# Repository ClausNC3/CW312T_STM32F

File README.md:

# CW312T-STM32F

This board supports the STMicroelectronics STM32F microcontroller. The default build
has the STMicroelectronics STM32F405VGT6, which has 1MB flash and 192kB SRAM.

---

## Specifications

|Feature|Notes/Range|
|-|-|
|Target Device|STM32F405VGT6|
|Target Architecture|Arm Cortex-M4|
|Vcc|3.3V|
|Programming|STM32F Serial Bootloader, JTAG or SWD|
|Hardware Crypto|No|
|Availability|Standalone|
|Status|Released|
|Shunt|10Ω|

---

## Power Supply

---

## Programming

### **ChipWhisperer Programmer via Bootloader**

See further down this page for details.

### **JTAG Programmer**

The 20-pin JTAG port (HDR6 on CW313 Board) can be used with the
[ST-LINK/V2](https://www.digikey.com/product-detail/en/stmicroelectronics/ST-LINK-V2/497-10484-ND/2214535)
which is a low-cost JTAG programmer.

It is also possible to use other JTAG programmers such as OpenOCD. The
following command worked with an Olimex OpenOCD programmer and their
[OpenOCD for
Windows](https://www.olimex.com/Products/ARM/JTAG/ARM-USB-OCD-H/)
software:

    openocd
      -f path/to/board/files/cw313.cfg
      -c init
      -c targets
      -c "halt"
      -c "flash write_image erase path/to/firmware.hex"
      -c "verify_image path/to/firmware.hex"
      -c "reset run"
      -c shutdown

where the contents of `cw313.cfg` are

    source [find interface/olimex-arm-usb-ocd-h.cfg]
    source [find target/stm32f4x.cfg]
    reset_config srst_only

### **Programming via ChipWhisperer Bootloader**

The STM32F devices have a built-in bootloader, and the ChipWhisperer
software as of 3.5.2 includes support for this bootloader.

Important notes before we begin:

  - You MUST setup a clock and the serial lines for the chip. This is
    easily done by connecting to the scope and target, then running
    `default_setup()`:

<!-- end list -->

``` python
import chipwhisperer as cw
scope = cw.scope
target = cw.target(scope)
scope.default_setup()
```

Run the following python code once you have the scope and target set up:

``` python
prog = cw.programmers.STM32FProgrammer
cw.program_target(scope, prog, "<path to fw hex file>")
```

---

## Schematic

The schematic is available as a [PDF](CW312T-STM32F.pdf) or below as an image:

---

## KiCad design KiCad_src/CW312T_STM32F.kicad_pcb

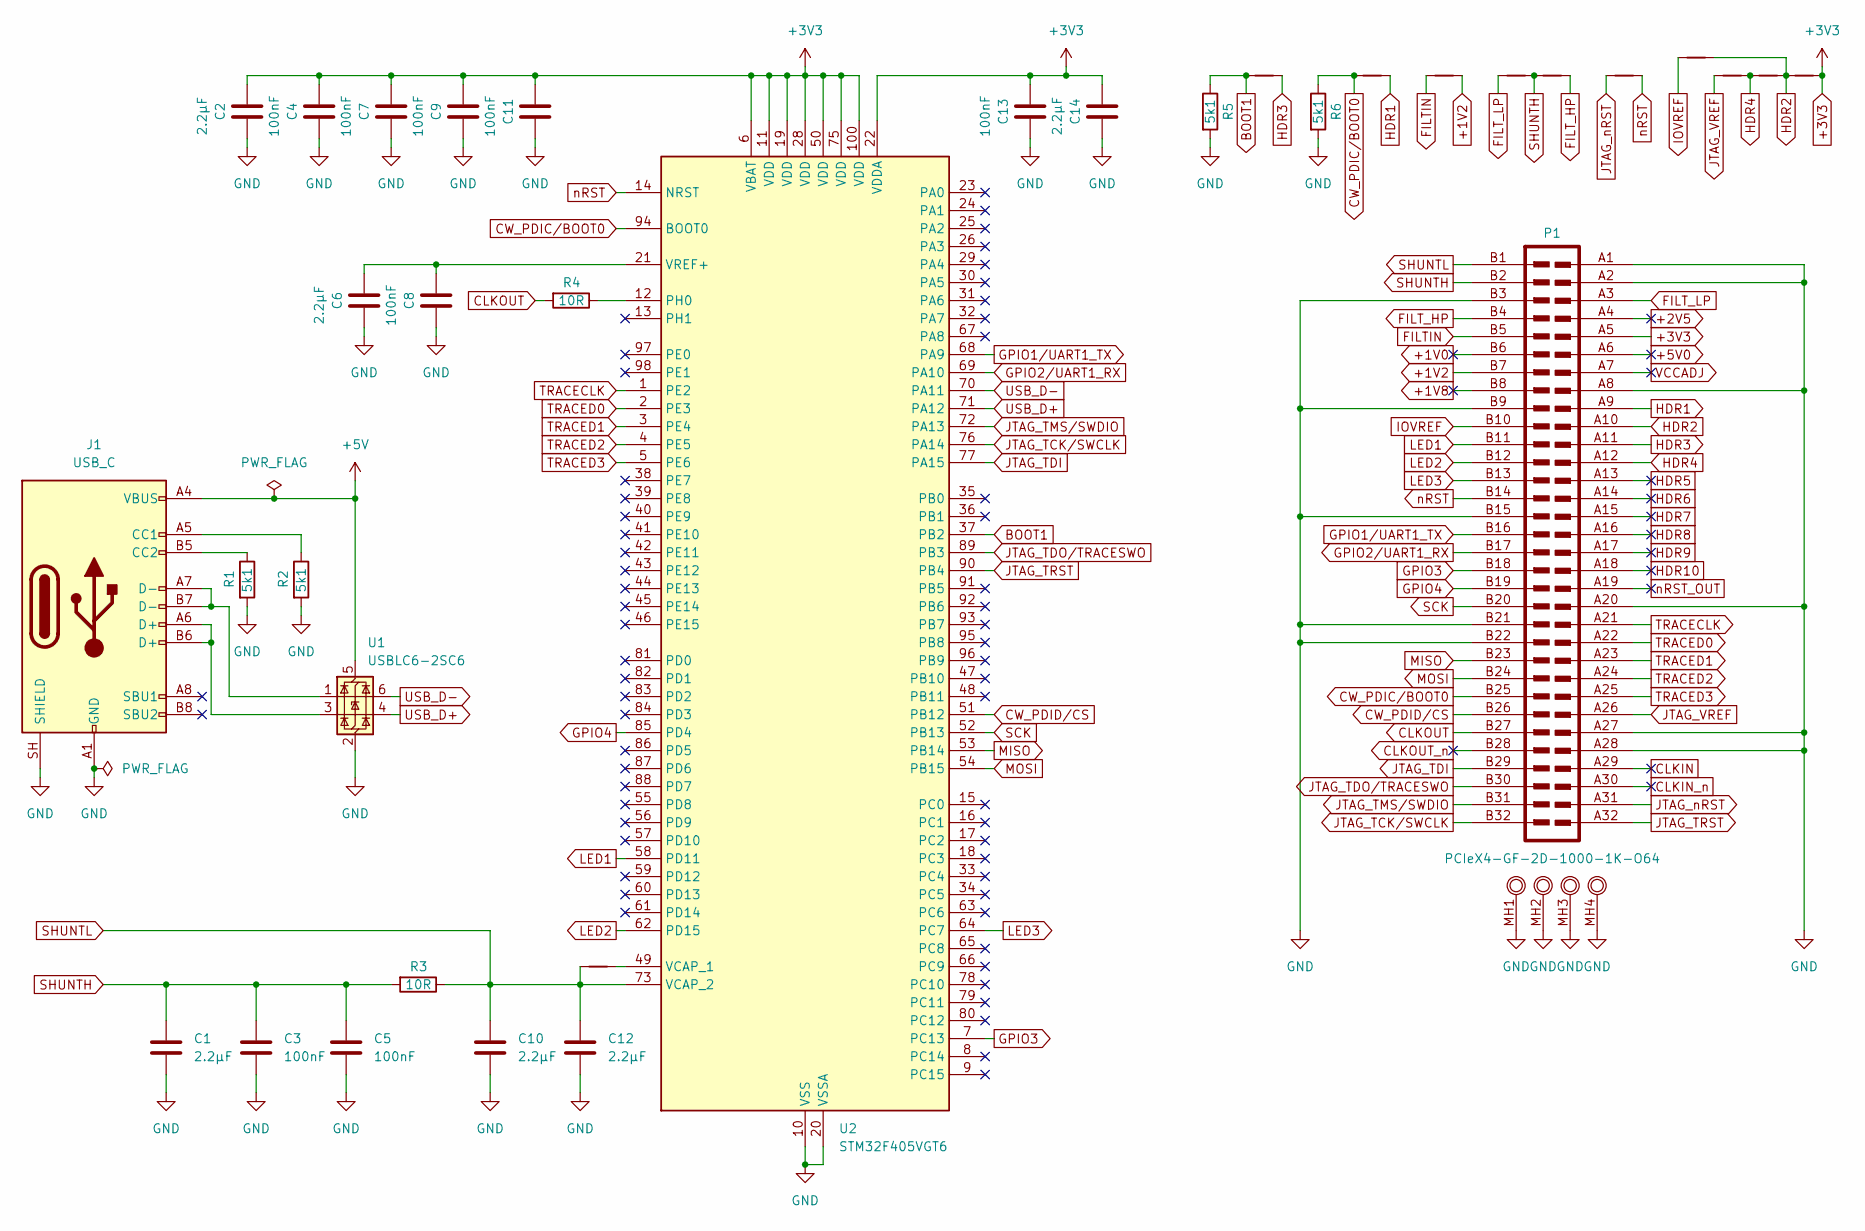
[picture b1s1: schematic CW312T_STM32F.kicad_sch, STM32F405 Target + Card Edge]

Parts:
C1, C2, C6, C10, C12, C14: 2.2μF; C_0603_1608Metric
C3, C4, C5, C7, C8, C9, C11, C13: 100nF; C_0603_1608Metric
J1: USB_C; USB_C_Receptacle_GCT_USB4105-xx-A_16P_TopMnt_Horizontal
NT1, NT2, NT3, NT4, NT5, NT6, NT7, NT8, NT9, NT10, NT11: NetTie_2; NetTie-2_SMD_Pad0.5mm
P1: PCIeX4-GF-2D-1000-1K-O64; CW312_CardEdge
R1, R2, R5, R6: 5k1; R_0603_1608Metric
R3, R4: 10R; R_0603_1608Metric
U1: USBLC6-2SC6; SOT-23-6
U2: STM32F405VGT6; LQFP-100_14x14mm_P0.5mm

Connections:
+1V0: P1.B6
+1V2: NT4.2, P1.B7
+1V8: P1.B8
+2V5: P1.A4
+3V3: C2.1, C4.1, C7.1, C9.1, C11.1, C13.1, C14.1, NT11.2, P1.A5, U2.6 (VBAT), U2.11 (VDD), U2.19 (VDD), U2.22 (VDDA), U2.28 (VDD), U2.50 (VDD), U2.75 (VDD), U2.100 (VDD)
+5V: J1.A4 (VBUS), J1.A9 (VBUS), J1.B4 (VBUS), J1.B9 (VBUS), U1.5 (VBUS)
+5V0: P1.A6
BOOT1: NT2.1, R5.1, U2.37 (PB2)
CLKIN: P1.A29
CLKIN_n: P1.A30
CLKOUT: P1.B27, R4.2
CLKOUT_n: P1.B28
CW_PDIC/BOOT0: NT3.1, P1.B25, R6.1, U2.94 (BOOT0)
CW_PDID/CS: P1.B26, U2.51 (PB12)
FILTIN: NT4.1, P1.B5
FILT_HP: NT6.2, P1.B4
FILT_LP: NT5.1, P1.A3
GND: C1.2, C2.2, C3.2, C4.2, C5.2, C6.2, C7.2, C8.2, C9.2, C10.2, C11.2, C12.2, C13.2, C14.2, J1.A1 (GND), J1.A12 (GND), J1.B1 (GND), J1.B12 (GND), J1.SH (SHIELD), P1.A1, P1.A2, P1.A8, P1.A20, P1.A27, P1.A28, P1.B3, P1.B9, P1.B15, P1.B21, P1.B22, P1.MH1 (MH), P1.MH2 (MH), P1.MH3 (MH), P1.MH4 (MH), R1.2, R2.2, R5.2, R6.2, U1.2 (GND), U2.10 (VSS), U2.20 (VSSA), U2.27 (VSS), U2.74 (VSS), U2.99 (VSS)
GPIO1/UART1_TX: P1.B16, U2.68 (PA9)
GPIO2/UART1_RX: P1.B17, U2.69 (PA10)
GPIO3: P1.B18, U2.7 (PC13)
GPIO4: P1.B19, U2.85 (PD4)
HDR1: NT3.2, P1.A9
HDR2: NT8.2, NT10.2, NT11.1, P1.A10
HDR3: NT2.2, P1.A11
HDR4: NT9.2, NT10.1, P1.A12
HDR5: P1.A13
HDR6: P1.A14
HDR7: P1.A15
HDR8: P1.A16
HDR9: P1.A17
HDR10: P1.A18
IOVREF: NT8.1, P1.B10
JTAG_TCK/SWCLK: P1.B32, U2.76 (PA14)
JTAG_TDI: P1.B29, U2.77 (PA15)
JTAG_TDO/TRACESWO: P1.B30, U2.89 (PB3)
JTAG_TMS/SWDIO: P1.B31, U2.72 (PA13)
JTAG_TRST: P1.A32, U2.90 (PB4)
JTAG_VREF: NT9.1, P1.A26
JTAG_nRST: NT7.1, P1.A31
LED1: P1.B11, U2.58 (PD11)
LED2: P1.B12, U2.62 (PD15)
LED3: P1.B13, U2.64 (PC7)
MISO: P1.B23, U2.53 (PB14)
MOSI: P1.B24, U2.54 (PB15)
unnamed: J1.A5 (CC1), R2.1
unnamed: J1.B5 (CC2), R1.1
unnamed: J1.A6 (D+), J1.B6 (D+), U1.3 (I/O2)
unnamed: J1.A7 (D-), J1.B7 (D-), U1.1 (I/O1)
unnamed: R4.1, U2.12 (PH0)
unnamed: NT1.2, U2.49 (VCAP_1)
unnamed: C6.1, C8.1, U2.21 (VREF+)
SCK: P1.B20, U2.52 (PB13)
SHUNTH: C1.1, C3.1, C5.1, NT5.2, NT6.1, P1.B2, R3.2
SHUNTL: C10.1, C12.1, NT1.1, P1.B1, R3.1, U2.73 (VCAP_2)
TRACECLK: P1.A21, U2.1 (PE2)
TRACED0: P1.A22, U2.2 (PE3)
TRACED1: P1.A23, U2.3 (PE4)
TRACED2: P1.A24, U2.4 (PE5)
TRACED3: P1.A25, U2.5 (PE6)
USB_D+: U1.4 (I/O2), U2.71 (PA12)
USB_D-: U1.6 (I/O1), U2.70 (PA11)
VCCADJ: P1.A7
nRST: NT7.2, P1.B14, U2.14 (NRST)
nRST_OUT: P1.A19

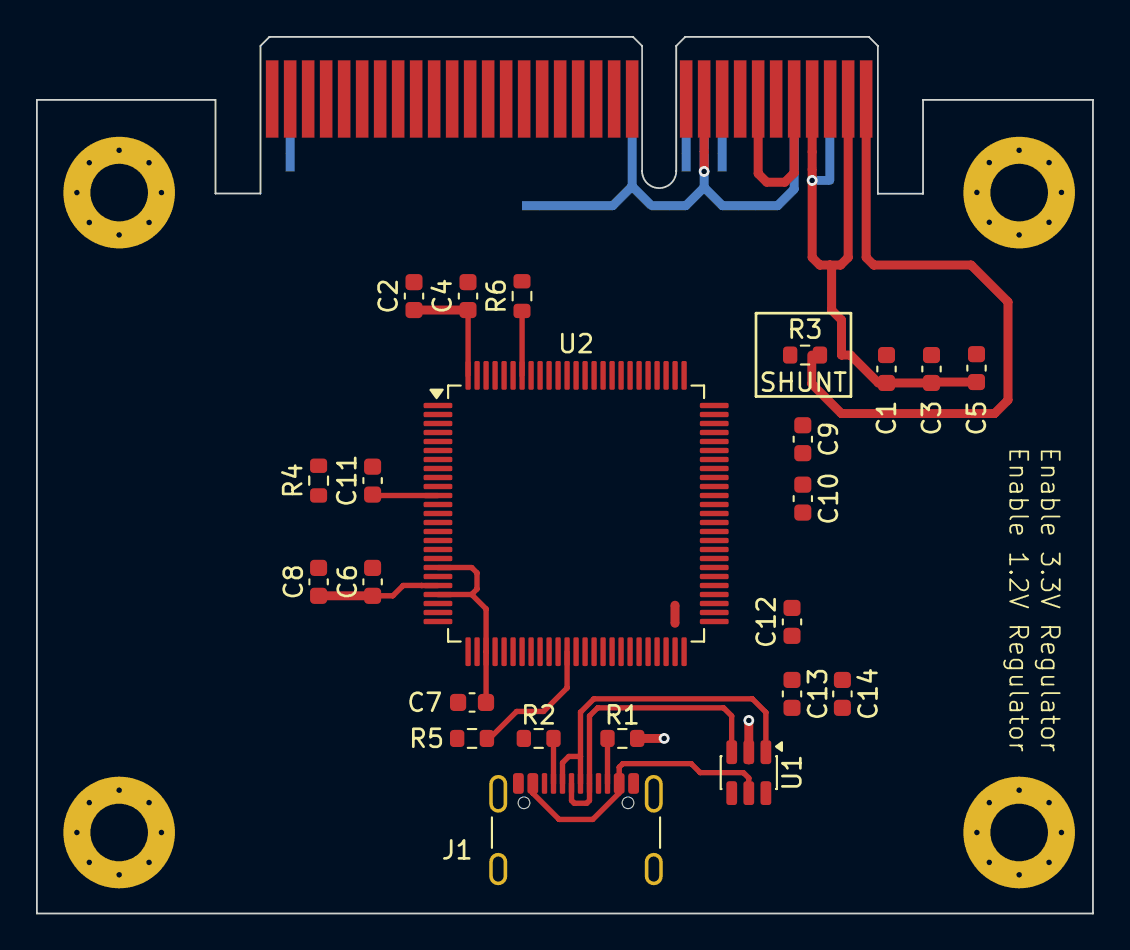
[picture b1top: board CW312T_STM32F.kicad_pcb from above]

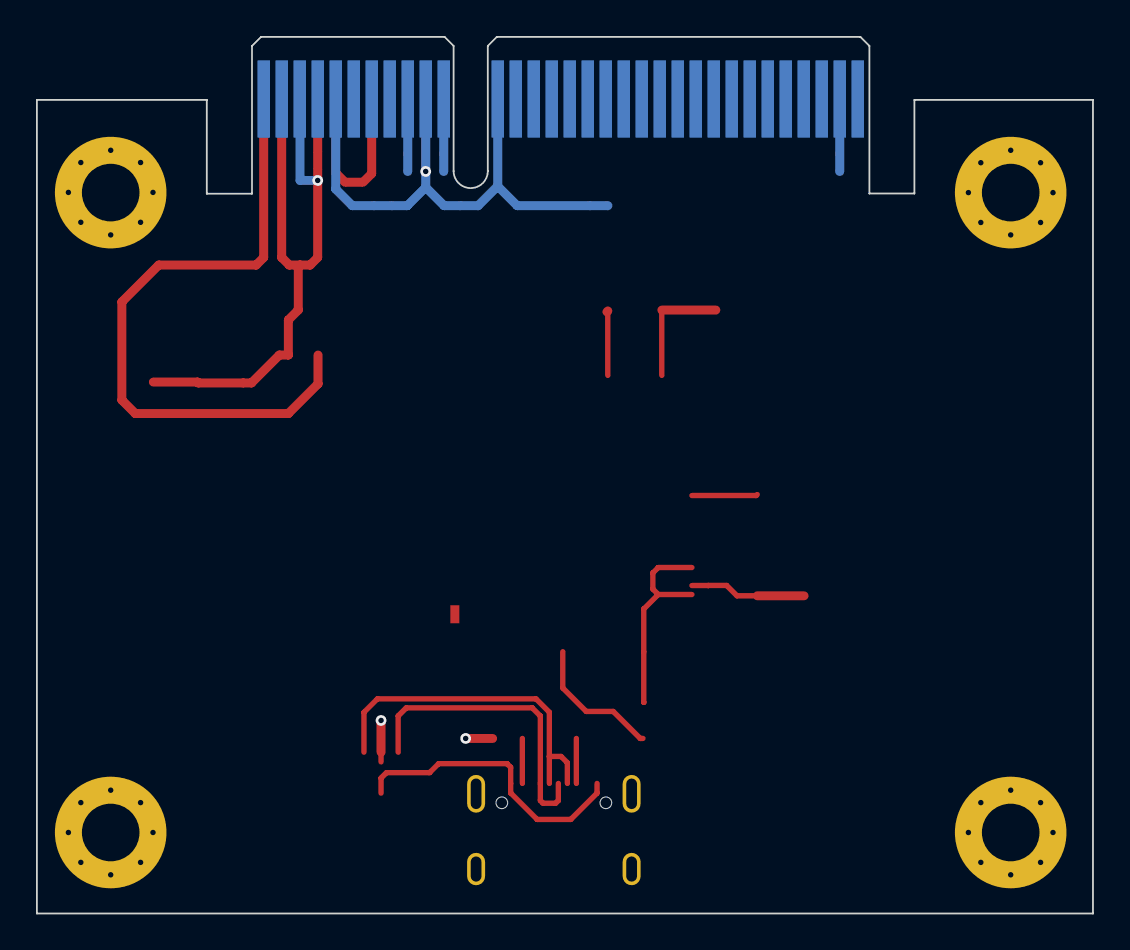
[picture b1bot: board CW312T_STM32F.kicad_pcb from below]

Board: 2 copper layers, 58.7 x 48.7 mm, 35 parts (7 on the bottom side), 50 nets.

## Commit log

2026-04-26 first push
2026-04-26 add Render image
2026-04-26 Edit Readme
